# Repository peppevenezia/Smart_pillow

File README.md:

# Posture Monitoring System - PsoCuscino

This project was developed in collaboration with https://github.com/giovanni6inve , https://github.com/Sebastian-Gerletti , https://github.com/alecac96

## Aim of the project

Sitting posture classifiaction for behavioral analysis of desk workers, in particuar working at PC. Data is collected from 11 FSR sensors (Force Sensitive Resistors) arranged on a chair.

## Hardware and set-up
<figure>

<figcaption>Force Sensitive Resistor (FSR).</figcaption>

</figure>

FSR sensors (strain gauges) are read by voltage partitioning on a resistance of 10kohm (Rb) and high impedence readout provided by the PSoC.

<figure>

<figcaption>Vin is 5V alimentation, the variable resistance (FSR) is Ra.</figcaption>

</figure>

The 11 sensors are iteratively read by an AMUX which feeds the analog signal for conversion to the ADC DelSig configured at 16 bit resolution, Multi Sample (since independent sensors) and 10000SPS. The sampling period is of 300ms, set by timer ISR, at which all sensors are read, sampled and sent to the GUI using UART serial communication (baud rate of 115200bps).

For easy and simple interfacing with the user (namely connection research, connected, sampling and calibration) a LED was set using a variable PWM. 

The sensor disposition upon the chair is symmetric w.r.t. the sagittal plane and while maintaining a base disposition as in figure, their precise position was optimized for maximum activation according to physiological pressure points and allowing for interuser variability: namely male/female, height ranges from 154cm to 200cm and weights from 49kg to 93kg.

<figure>

<figcaption>Where "S" stands for the FSR sensor and 0 is for the space on the hard surface, where they are attached to with tape, in between them.</figcaption>

</figure>

## Firmware (PSoC)

Connection between GUI and PSoC is dealt with automatically: the GUI sends "v" by UART, PSoC transmits "Posture$$$" in responce; if this "handshaking" (mutual recognition happens) connecion is confirmed by the GUI: "e" is received.

Once "b" is received all sensors are sampled at 3.33Hz and the 16bit value for each one is unpacked into 2 bytes for serial communication. During the first 4.5s, during which the subject is already seated, the calibration procedure takes place: it is aimed at rescaling all sensors' values by the same factor in order to exploit the whole 16 bit range, the factor is obtained dividing the desired maximum output (65535) by the actual global maximum among the sampled values for all sensors (15 samples * 11 sensors). By doing so a heavy subject and a lighter one will be associated with an equally intense heatmap (considering the values for the higher pressure points).

The synchrony and activation of all this is given by the a timer which is turned on upon "b" receval and off with "s".

## Software (GUI)
(Particular attention was given to interoperability of the whole process among different operating systems).

Upon launching the application, in order to find the port to which the PSoC is connected to, all the list of ports is iterated and the char "v" is sent to each port with a hardcoded baud rate (shared by the PSoC). Ports are passed by if a limit of time spent within them is reached; if "Posture$$$" is received connection is confirmed with that port (PSoC's one) by sending "e" to it.

To then communicate with the device a user-friendly interface is presented: "start" and "stop" buttons, which transmit "b" and "s" respectively; as for visualization, once "start" has been pressed the heatmap given by the sensors' padded and interpolated (upsampled) data is presented; and below the heatmap the posture prediction is written having as classes: "correct", "leaning forwards", "leaning backwards", "leaning right" and "leaning left". Notice the sensors' set-up, should also guarantee the recognition of crossed-legs posture but in order to train a network capable to distinguish between leaning sideways and doing so with crossed legs much more data would have been necessary to obtain satisfying performances since a more complex model would have been necessary to face the more complex task.
#### Data decoding
Each sensor value is kept in 16 bit format, so the heatmap scale goes from 0 to 65535; however since a string of 48 chars containing all sensors' data scopmosed in MSB and LSB (each then composed by 2 chars) is received, the 11 sensors values need to be re-assembled (reverse the shift and masking done at PSoC level) after cropping the head and the tail (each of 2 fixed chars).
#### Interpolation (upsampling)
Plotting only the 11 values which are sampled from the sensors is not sufficient for a clear and interpretable image, for this reason upsampling is required, the best method to replicte true weight distribution proved to be interpolation done using scipy's griddata function and an appropriate padding.

Padding is done, by linealy combining the sensors' values according to the matrix in the figure above and accounting for borders using a multiplicative decay. This was done to space the sensors' positions both from borders and from each other when feeding them to griddata which then performs a much more complex interpolation accounting for the exact positions of sensors (measured on the chair) and custom padding  (approximated from the previous measurements) and exploiting a non linear combination of values. A 41x45 image is thus obtained.

<figure>

<figcaption>GUI: buttons, heatmap, class prediction.</figcaption>

</figure>

#### Posture classification
To classify the posture among the aforementioned classes a neural network was implemented. A prediction is provided for each frame (300ms) by inserting the prediction "pipeline" within the iterating thread of the GUI which reads, interpolates and plots data. The pipeling includes data rescaling other than the actual prediction and it does so by using the parameters obtained from the training set to normalize the data and the saved model.

The model to classify each frame is a neural network which was trained,tuned and tested with data from 15 users, split in 2 disjoint and stratified sets (after informed consent signing).

The protocol to acquire the training data, and quite intuitively to label it, was to sample 1min (so 200 samples per position) in each position (after calibration) in the same order reported above.

Notice: for the model training a few considerations must be made regarding the replicability of our procedure:\
as regards data acquisitions for the training dataset (done with the above protocol) once "stop" has been pressed on the GUI the "export file" button is available and it automatically saves the User's data (name of the user to be specified when running the application from terminal where, if no data for that user has already been obtained, the corresponding folder is created) at a path related to where the code is run from, for this reason coherence in the path explicitaded in posture_net.py, when loading the data, is required.

Furthermore the data we collected is not uploaded in the repository for privacy reasons.
Regardless of this the pretrained model is uploaded for online application on new data.

<figure>

<figcaption>Model's architecture: average pooling from 41x45 (input) to 20x22; average pooling to 10x11 (similar to local baricenters extraction with decreasing resolution); flatten; dense layers (100 - 50 - 5) where the last layer has softmax activation to obtain the output probabilities of the 5 classes.</figcaption>

</figure>

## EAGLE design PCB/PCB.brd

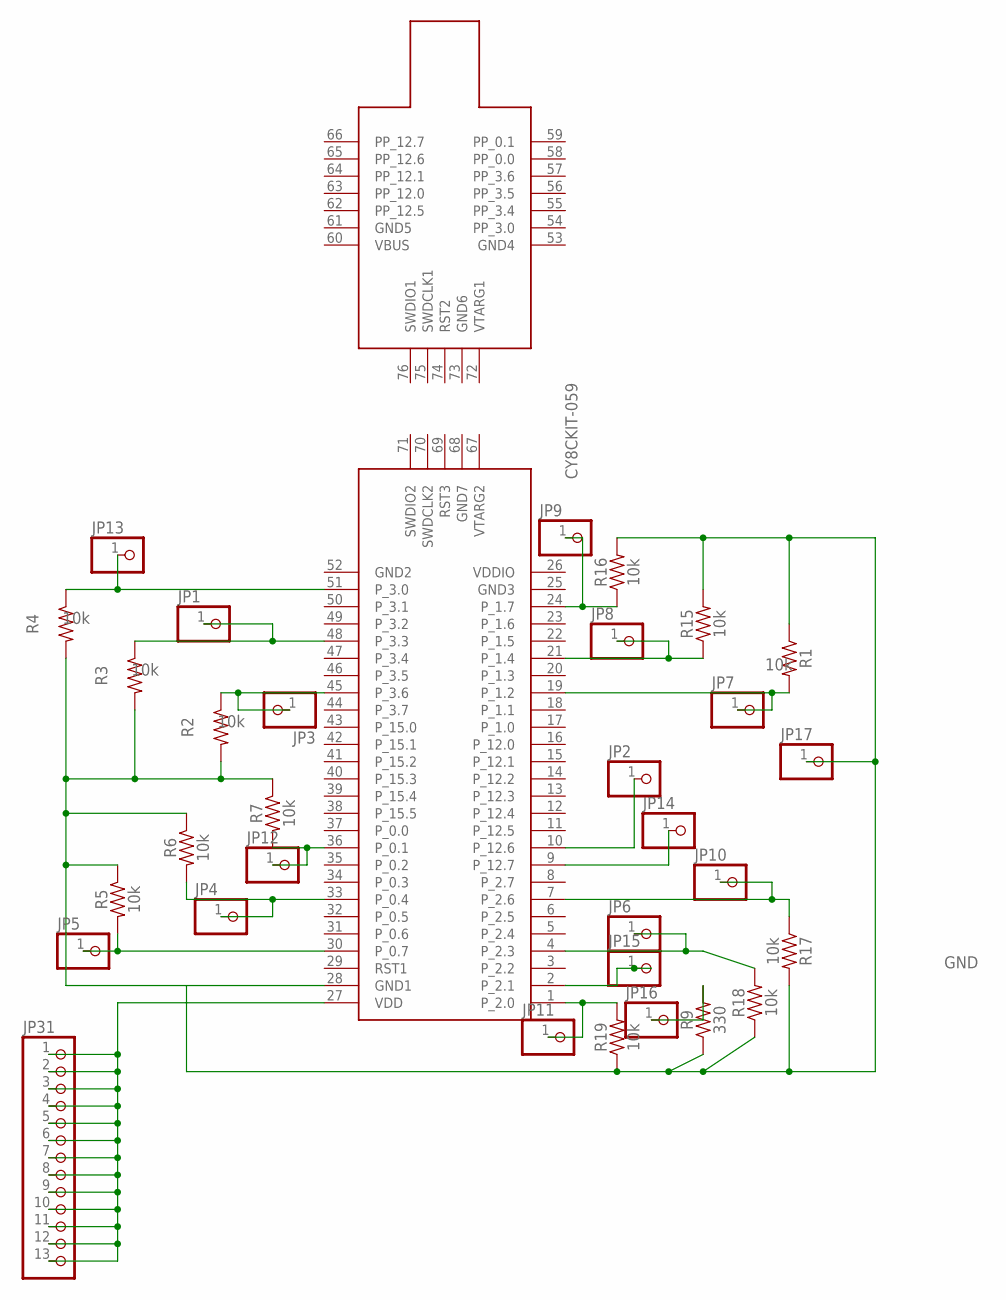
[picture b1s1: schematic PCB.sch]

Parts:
JP1, JP2, JP3, JP4, JP5, JP6, JP7, JP8, JP9, JP10, JP11, JP12, JP13, JP14, JP15, JP16, JP17: PINHD-1X1; 1X01
JP31: PINHD-1X13; 1X13
R1, R2, R3, R4, R5, R6, R7, R15, R16, R17, R18, R19: 10k; AXIAL-0.3
R9: 330; AXIAL-0.3
U$1: CY8CKIT-059

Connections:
GND: JP17.1, R1.P$1 (1), R2.P$2 (2), R3.P$2 (2), R4.P$2 (2), R5.P$1 (1), R6.P$1 (1), R7.P$1 (1), R9.P$1 (1), R15.P$2 (2), R16.P$2 (2), R17.P$2 (2), R18.P$1 (1), R19.P$1 (1), U$1.28 (GND1)
unnamed: JP3.1, R2.P$1 (1), U$1.45 (P_3.6)
unnamed: JP4.1, R6.P$2 (2), U$1.33 (P_0.4)
unnamed: JP12.1, R7.P$2 (2), U$1.36 (P_0.1)
unnamed: JP5.1, R5.P$2 (2), U$1.30 (P_0.7)
unnamed: JP1.1, R3.P$1 (1), U$1.48 (P_3.3)
unnamed: JP9.1, R16.P$1 (1), U$1.24 (P_1.7)
unnamed: JP8.1, R15.P$1 (1), U$1.21 (P_1.4)
unnamed: JP7.1, R1.P$2 (2), U$1.19 (P_1.2)
unnamed: JP13.1, R4.P$1 (1), U$1.51 (P_3.0)
unnamed: JP11.1, R19.P$2 (2), U$1.1 (P_2.0)
unnamed: JP6.1, R18.P$2 (2), U$1.4 (P_2.3)
unnamed: JP10.1, R17.P$1 (1), U$1.7 (P_2.6)
unnamed: JP2.1, U$1.10 (P_12.6)
unnamed: JP15.1, U$1.2 (P_2.1)
unnamed: JP16.1, R9.P$2 (2)
unnamed: JP14.1, U$1.9 (P_12.7)
unnamed: JP31.1, JP31.2, JP31.3, JP31.4, JP31.5, JP31.6, JP31.7, JP31.8, JP31.9, JP31.10, JP31.11, JP31.12, JP31.13, U$1.27 (VDD)

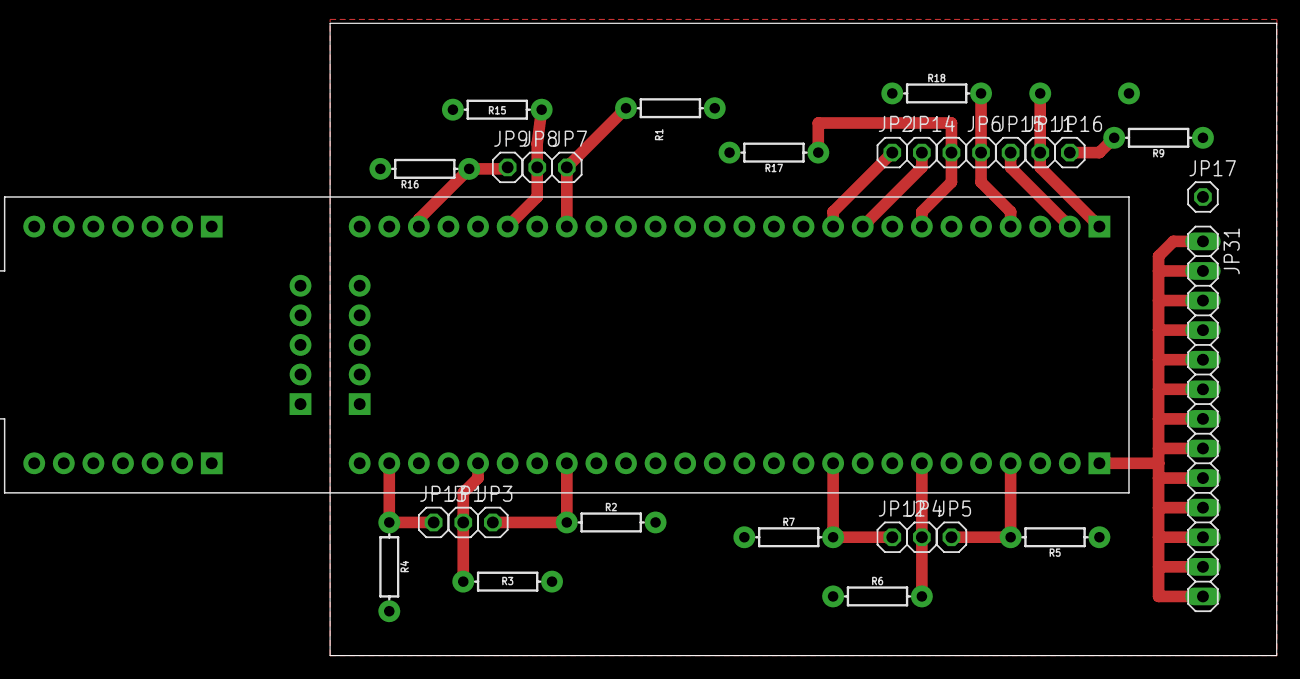
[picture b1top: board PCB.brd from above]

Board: 2 copper layers, 81.3 x 54.3 mm, 32 parts (1 on the bottom side), 18 nets.

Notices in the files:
parts and their libraries:
SparkFun-Resistors: Licensing: Creative Commons ShareAlike 4.0 International - https://creativecommons.org/licenses/by-sa/4.0
